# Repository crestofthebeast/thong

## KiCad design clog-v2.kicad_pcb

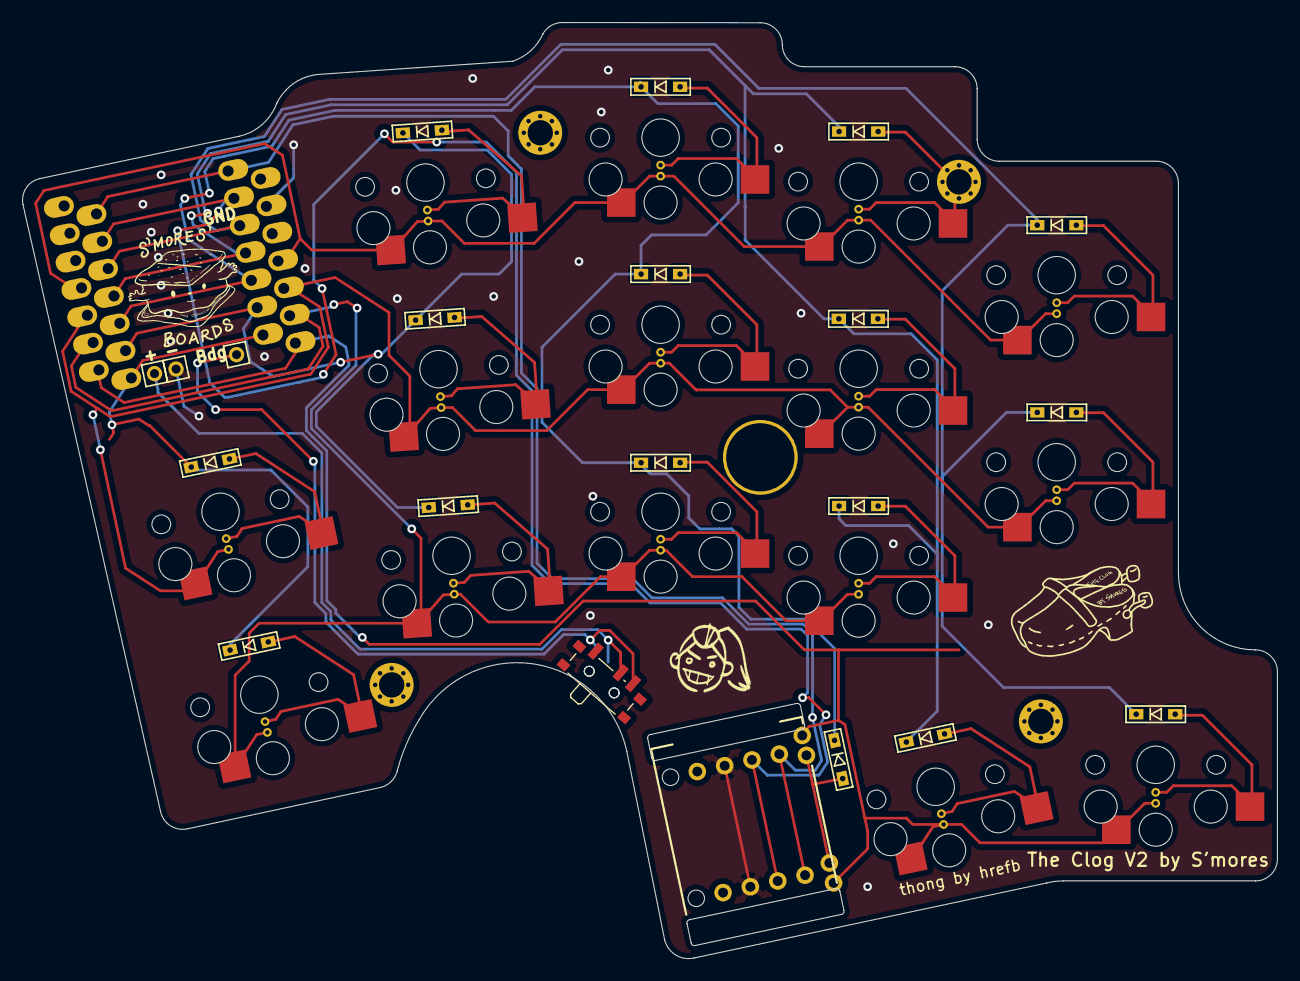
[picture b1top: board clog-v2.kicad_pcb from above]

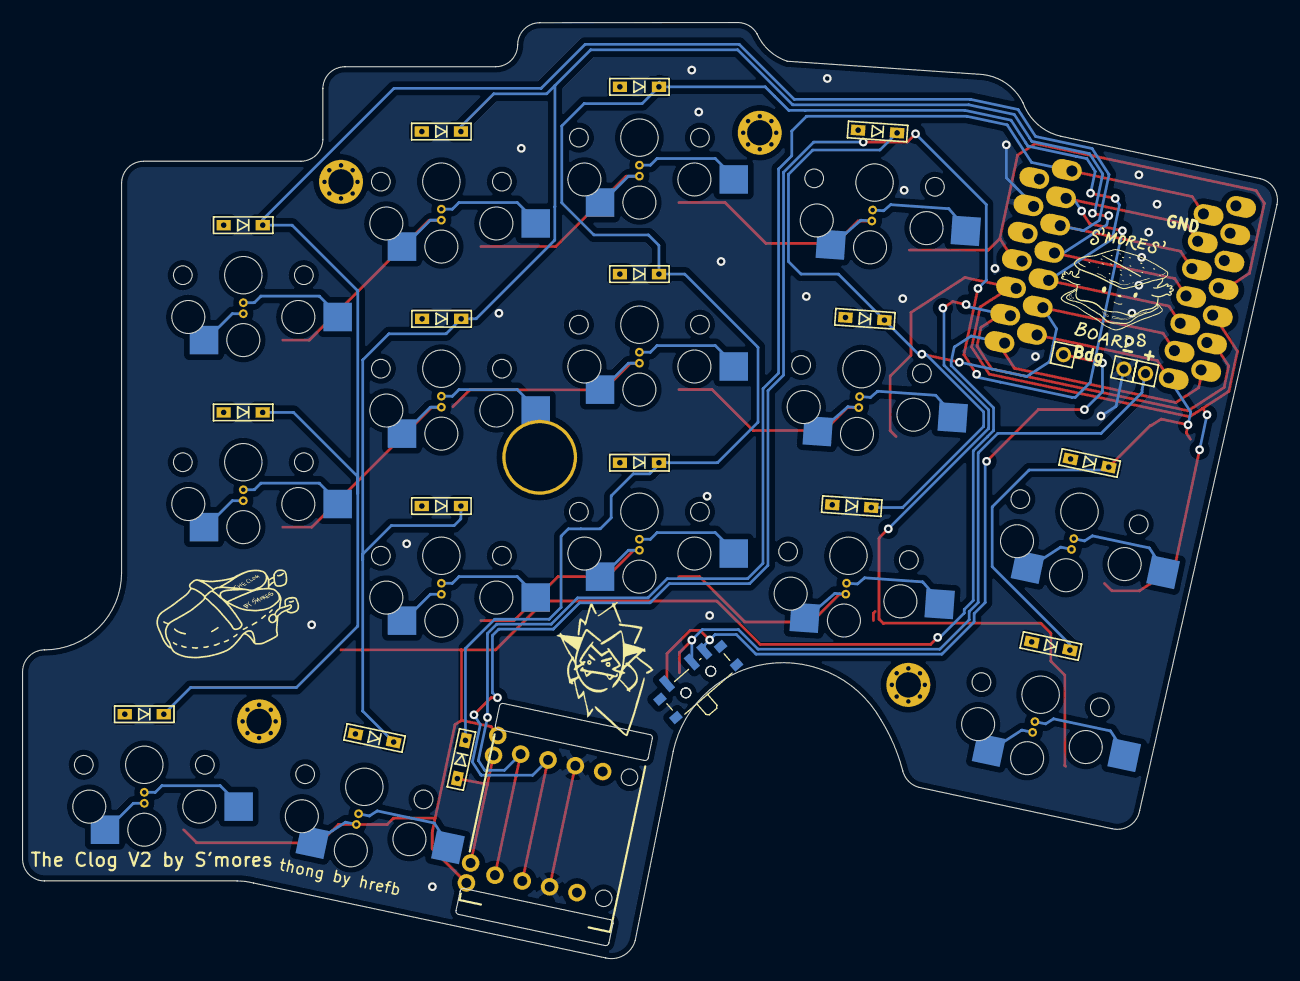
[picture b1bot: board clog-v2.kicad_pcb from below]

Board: 2 copper layers, 114.1 x 85.1 mm, 46 parts (3 on the bottom side), 15 nets.

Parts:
+1: MountingHole_Pad; single-pin
-1: MountingHole_Pad; single-pin
D2, D3, D4, D5, D6, D7, D8, D9, D10, D11, D12, D13, D14, D16, D17, D18: 1N4148W; smd-diode
PW1: MountingHole_Pad; single-pin
Ref**: Val**; m2-hole
Ref**#2, Ref**#4, Ref**#5: Val**; m2-hole
Ref**#3: Val**; catra_half
Ref**#6: Val**; adora_half
SW2, SW3, SW4, SW5, SW6, SW7, SW8, SW9, SW10, SW11, SW12, SW13, SW14, SW17, SW18: Switch; pg1350-DH
SW16_1, SW16_2: EVQWGD001; evq
SW20, SW21: SW_SPDT; SW_SPDT_PCM12
U1, U2: xiao-ble

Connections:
Bat+: +1.1, SW20.2 (B), SW21.2 (B)
Col1: D6.1 (K), D11.1 (K), U1.7 (B8_TX/1.11), U2.7 (B8_TX/1.11)
Col2: D2.1 (K), D7.1 (K), D12.1 (K), U1.6 (A9_SCL/0.05_H), U2.6 (A9_SCL/0.05_H)
Col3: D3.1 (K), D8.1 (K), D13.1 (K), D16.1 (K), U1.5 (A8_SDA/0.04_H), U2.5 (A8_SDA/0.04_H)
Col4: D4.1 (K), D9.1 (K), D14.1 (K), D17.1 (K), U1.4 (A11/0.29), U2.4 (A11/0.29)
Col5: D5.1 (K), D10.1 (K), D18.1 (K), U1.3 (A10/0.28), U2.3 (A10/0.28)
EncL: SW16_1.A, SW16_2.A, U1.1 (A2/0.02_H), U2.1 (A2/0.02_H)
EncR: SW16_1.B, SW16_2.B, U1.2 (A4/0.03_H), U2.2 (A4/0.03_H)
GND: -1.1, SW16_1.C, SW16_2.C, U1.13 (GND), U2.13 (GND)
Power: PW1.1, SW20.3 (C), SW21.3 (C)
Row1: SW2.1, SW3.1, SW4.1, SW5.1, U1.11 (A6_MOSI/1.15), U2.11 (A6_MOSI/1.15)
Row2: SW6.1, SW7.1, SW8.1, SW9.1, SW10.1, U1.10 (A5_MISO/1.14), U2.10 (A5_MISO/1.14)
Row3: SW11.1, SW12.1, SW13.1, SW14.1, U1.9 (A7_SCK/1.13), U2.9 (A7_SCK/1.13)
Row4: SW16_1.S1, SW16_2.S1, SW17.1, SW18.1, U1.8 (B9_RX/1.12), U2.8 (B9_RX/1.12)
S16R: D16.2 (A), SW16_1.S2, SW16_2.S2

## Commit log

2023-04-29 init
